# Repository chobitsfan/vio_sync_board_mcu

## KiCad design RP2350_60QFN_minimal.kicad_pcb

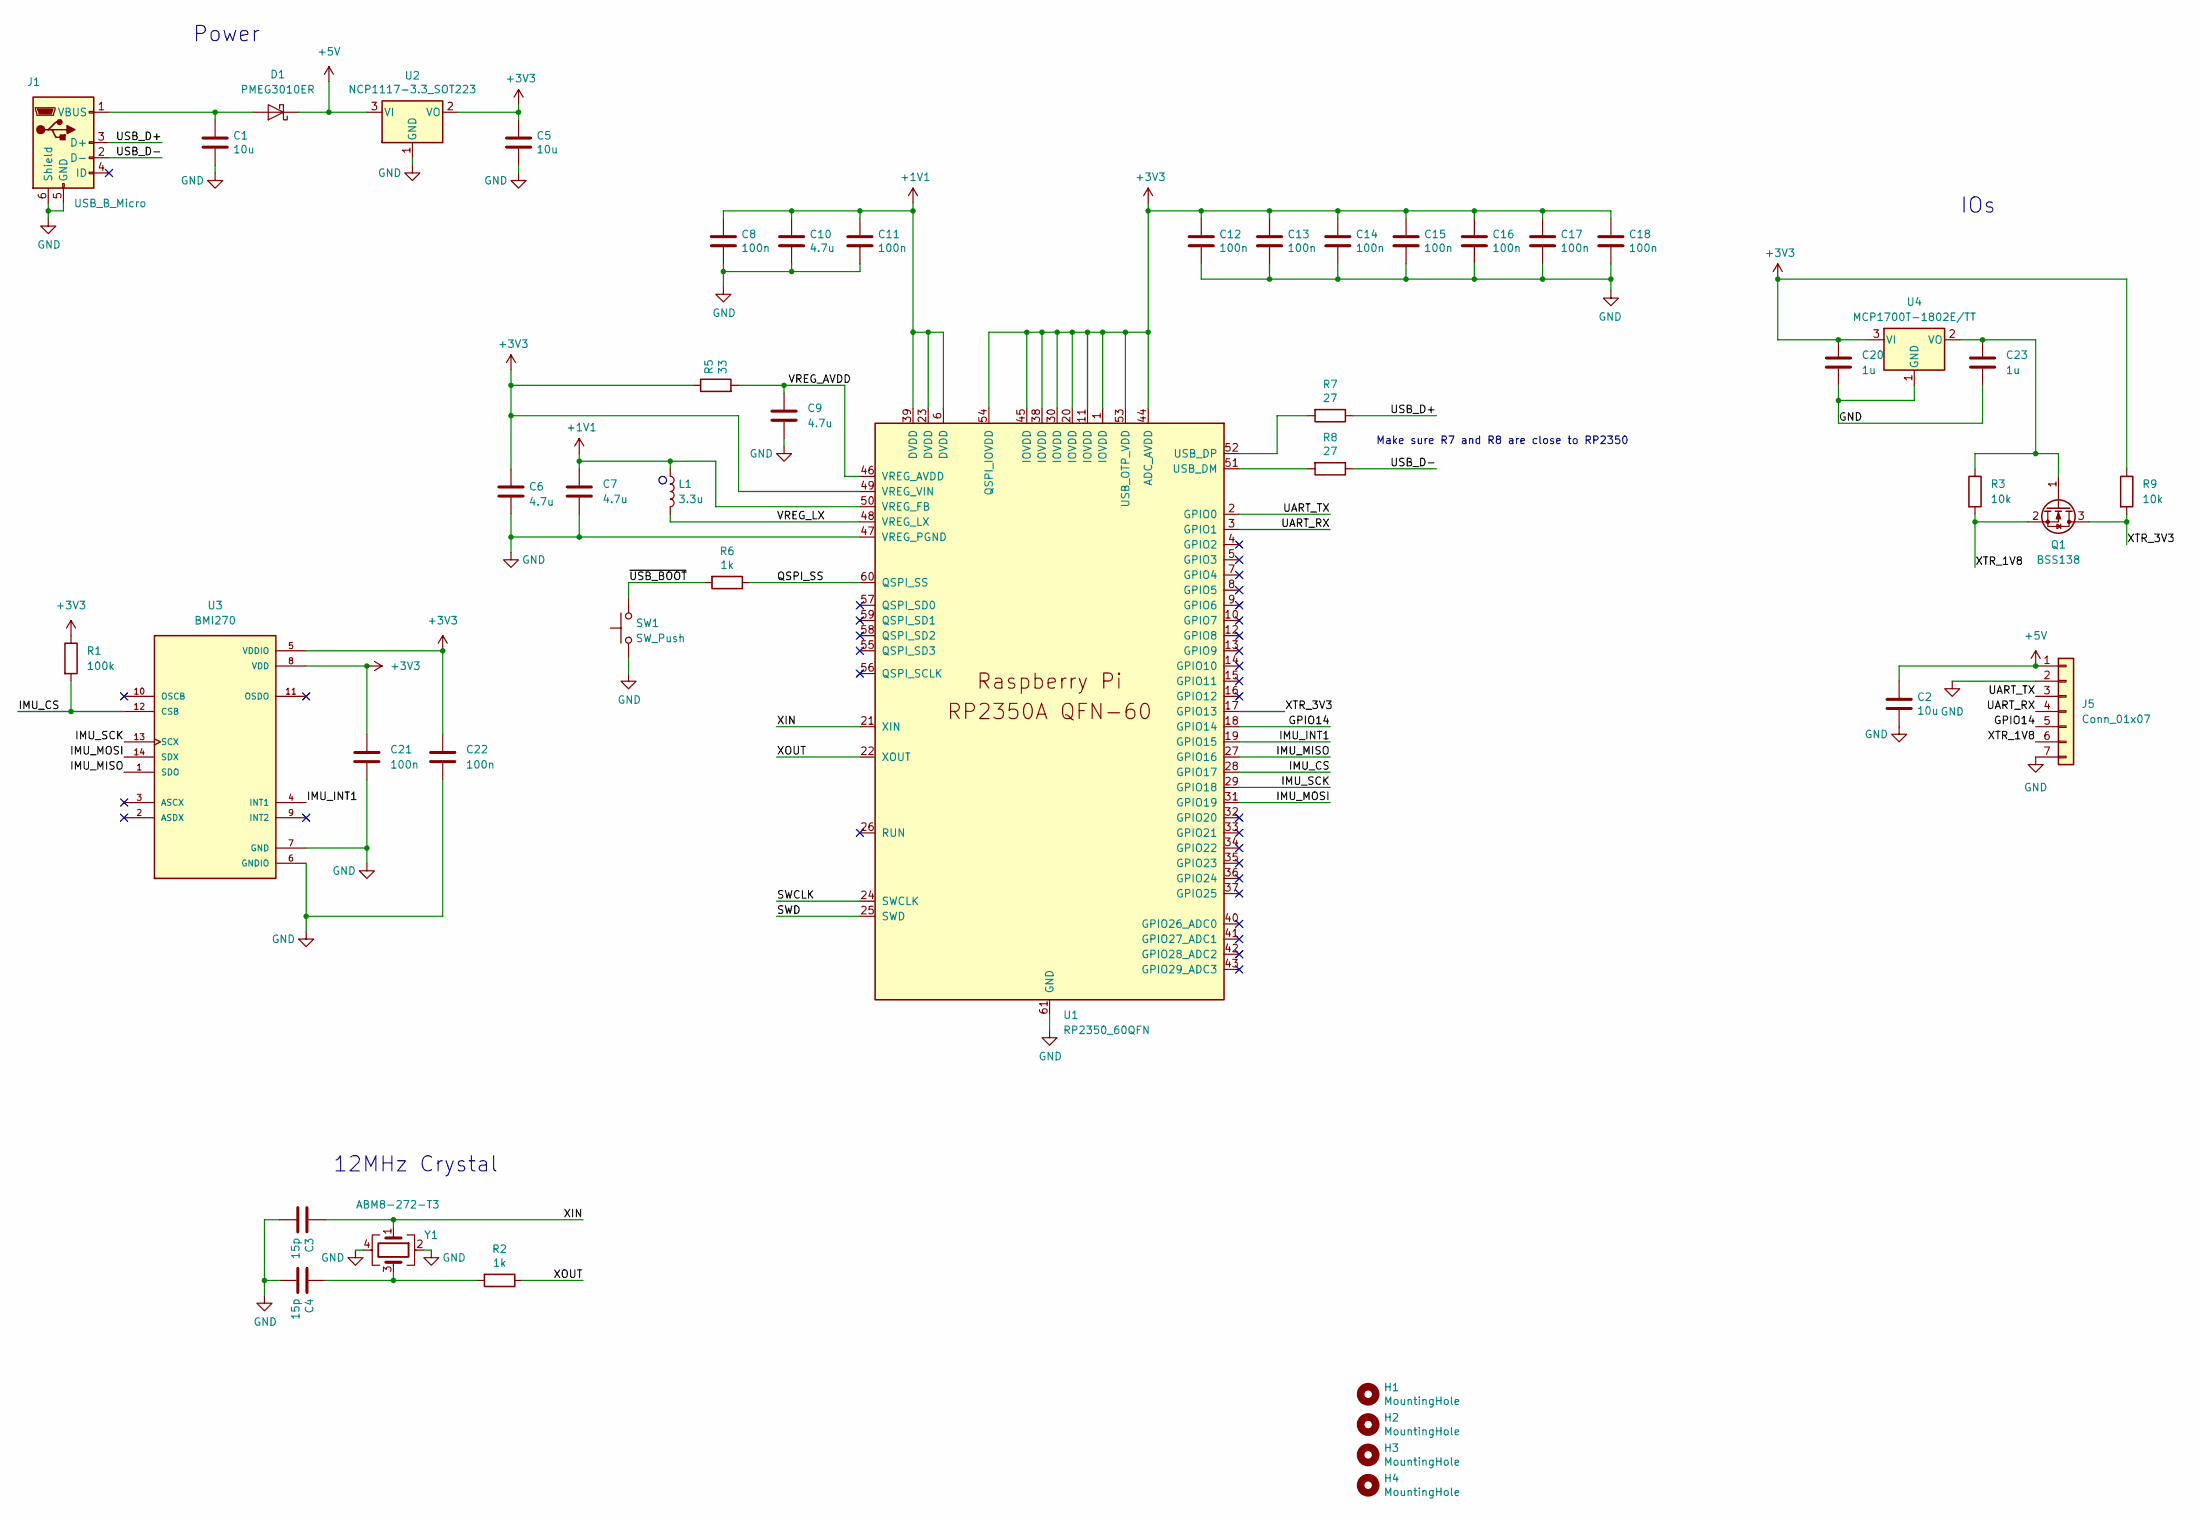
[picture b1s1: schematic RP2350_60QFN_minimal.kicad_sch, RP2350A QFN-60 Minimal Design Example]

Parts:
C1, C2, C5: 10u; C_0805_2012Metric
C3, C4: 15p; C_0402_1005Metric
C6, C7: 4.7u; C_0402_1005Metric_small_pads
C8, C11, C12, C13, C14, C15, C16, C17, C18: 100n; C_0402_1005Metric
C9, C10: 4.7u; C_0402_1005Metric
C20, C23: 1u; C_0805_2012Metric
C21, C22: 100n; C_0805_2012Metric
D1: PMEG3010ER; Nexperia_CFP3_SOD-123W
H1, H2, H3, H4: MountingHole; MountingHole_2.7mm_M2.5
J1: USB_B_Micro; USB_Micro-B_Amphenol_10103594-0001LF_Horizontal
J5: Conn_01x07; PinHeader_1x07_P2.54mm_Vertical
L1: 3.3u; L_pol_2016
Q1: BSS138; SOT-23
R1: 100k; R_0805_2012Metric
R2, R6: 1k; R_0402_1005Metric
R3, R9: 10k; R_0805_2012Metric
R5: 33; R_0402_1005Metric
R7, R8: 27; R_0402_1005Metric
SW1: SW_Push; SW_Push_1P1T_NO_Vertical_Wuerth_434133025816
U1: RP2350_60QFN; RP2350-QFN-60-1EP_7x7_P0.4mm_EP3.4x3.4mm_ThermalVias
U2: NCP1117-3.3_SOT223; SOT-223-3_TabPin2
U3: BMI270; XDCR_BMI270
U4: MCP1700T-1802E/TT; SOT-23
Y1: ABM8-272-T3; Crystal_SMD_3225-4Pin_3.2x2.5mm

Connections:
+1V1: C7.1, C8.1, C10.1, C11.1, L1.1, U1.6 (DVDD), U1.23 (DVDD), U1.39 (DVDD), U1.50 (VREG_FB)
+3V3: C5.1, C6.1, C12.1, C13.1, C14.1, C15.1, C16.1, C17.1, C18.1, C20.1, C21.1, C22.1, R1.1, R5.1, R9.1, U1.1 (IOVDD), U1.11 (IOVDD), U1.20 (IOVDD), U1.30 (IOVDD), U1.38 (IOVDD), U1.44 (ADC_AVDD), U1.45 (IOVDD), U1.49 (VREG_VIN), U1.53 (USB_OTP_VDD), U1.54 (QSPI_IOVDD), U2.2 (VO), U3.5 (VDDIO), U3.8 (VDD), U4.3 (VI)
+5V: C2.1, D1.1 (K), J5.1, U2.3 (VI)
/GPIO14: J5.5, U1.18 (GPIO14)
/IMU_CS: R1.2, U1.28 (GPIO17), U3.12 (CSB)
/IMU_INT1: U1.19 (GPIO15), U3.4 (INT1)
/IMU_MISO: U1.27 (GPIO16), U3.1 (SDO)
/IMU_MOSI: U1.31 (GPIO19), U3.14 (SDX)
/IMU_SCK: U1.29 (GPIO18), U3.13 (SCX)
/QSPI_SS: R6.1, U1.60 (QSPI_SS)
/SWCLK: U1.24 (SWCLK)
/SWD: U1.25 (SWD)
/UART_RX: J5.4, U1.3 (GPIO1)
/UART_TX: J5.3, U1.2 (GPIO0)
/USB_D+: J1.3 (D+), R7.1
/USB_D-: J1.2 (D-), R8.1
/VREG_AVDD: C9.1, R5.2, U1.46 (VREG_AVDD)
/VREG_LX: L1.2, U1.48 (VREG_LX)
/XIN: C3.1, U1.21 (XIN), Y1.1
/XOUT: R2.1, U1.22 (XOUT)
/XTR_1V8: J5.6, Q1.2 (S), R3.2
/XTR_3V3: Q1.3 (D), R9.2, U1.17 (GPIO13)
/~USB_BOOT: R6.2, SW1.2
GND: C1.2, C2.2, C3.2, C4.2, C5.2, C6.2, C7.2, C8.2, C9.2, C10.2, C11.2, C12.2, C13.2, C14.2, C15.2, C16.2, C17.2, C18.2, C20.2, C21.2, C22.2, C23.2, J1.5 (GND), J1.6 (Shield), J5.2, J5.7, SW1.1, U1.47 (VREG_PGND), U1.61 (GND), U2.1 (GND), U3.6 (GNDIO), U3.7 (GND), U4.1 (GND), Y1.2, Y1.4
unnamed: C4.1, R2.2, Y1.3
unnamed: C1.1, D1.2 (A), J1.1 (VBUS)
unnamed: C23.1, Q1.1 (G), R3.1, U4.2 (VO)
unnamed: R8.2, U1.51 (USB_DM)
unnamed: R7.2, U1.52 (USB_DP)

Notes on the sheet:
IOs
Make sure R7 and R8 are close to RP2350
12MHz Crystal
Power

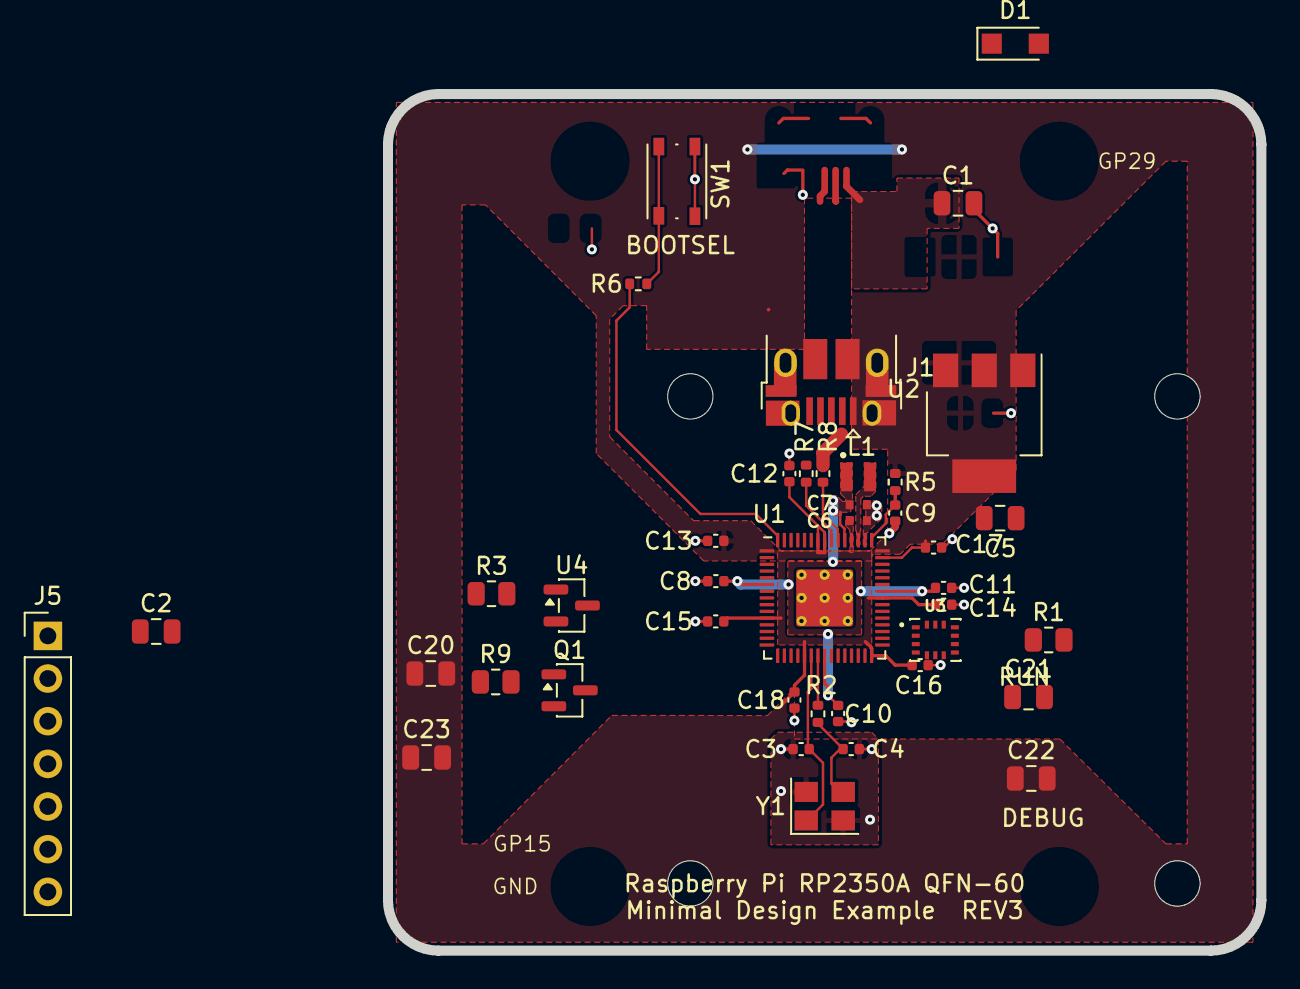
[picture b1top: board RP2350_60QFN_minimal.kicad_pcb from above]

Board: 2 copper layers, 52.0 x 51.0 mm, 45 parts (0 on the bottom side), 27 nets.

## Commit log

2026-04-24 try to place components
2026-05-15 working
